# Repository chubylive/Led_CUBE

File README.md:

Led_CUBE
========

rgb led cube

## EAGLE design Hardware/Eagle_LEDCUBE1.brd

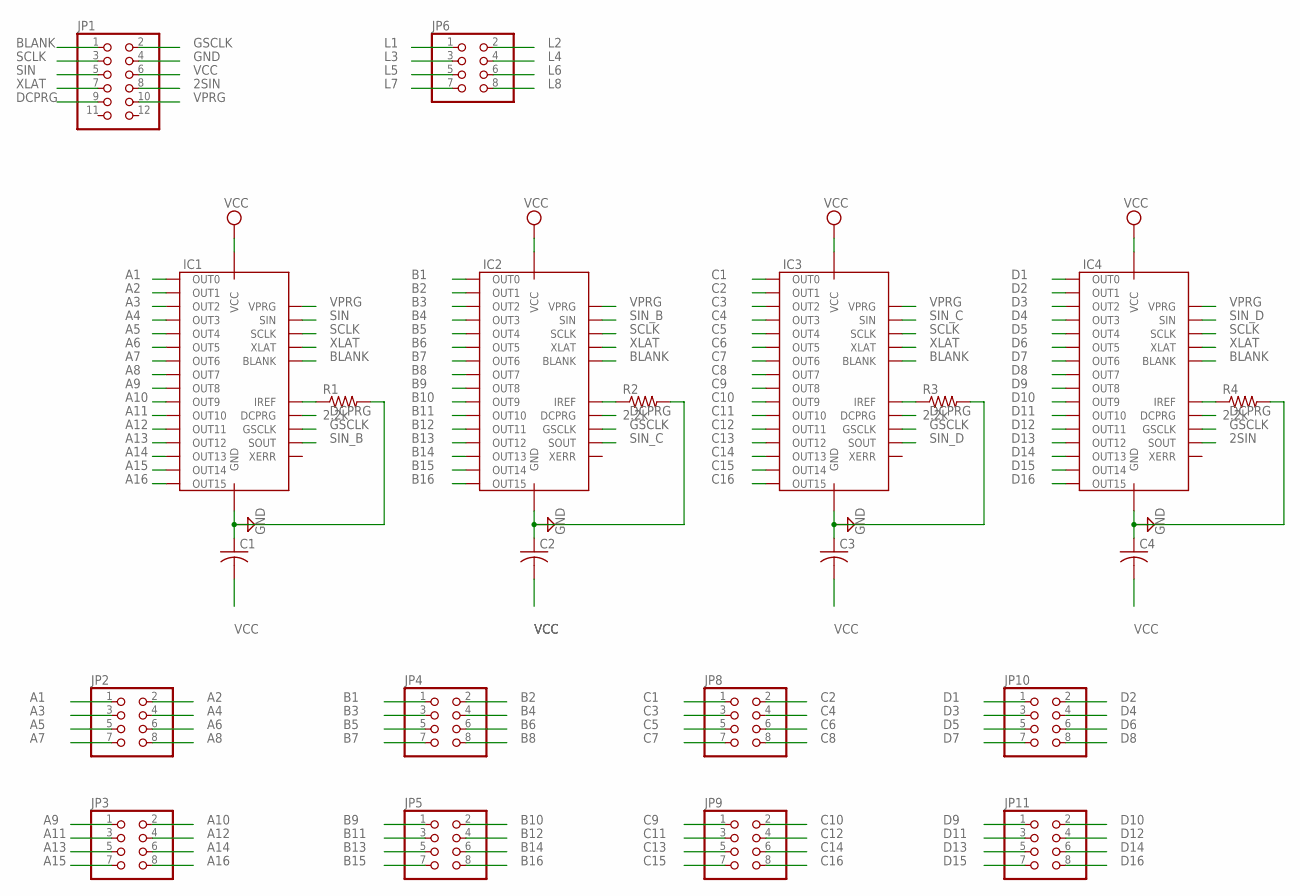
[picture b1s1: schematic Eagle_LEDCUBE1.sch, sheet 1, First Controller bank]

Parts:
C1, C2, C3, C4: C-USC0805K; C0805K
IC1, IC2, IC3, IC4: IC-PACKAGE_DIL28-1; IC-SSOP28
JP1: PINHD-2X6; 2X06
JP2, JP3, JP4, JP5, JP6, JP8, JP9, JP10, JP11: PINHD-2X4; 2X04
R1, R2, R3, R4: 2.2k; R0805

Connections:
2SIN: IC4.24 (SOUT), JP1.8; also elsewhere on the board
A1: IC1.7 (OUT0), JP2.1
A2: IC1.8 (OUT1), JP2.2
A3: IC1.9 (OUT2), JP2.3
A4: IC1.10 (OUT3), JP2.4
A5: IC1.11 (OUT4), JP2.5
A6: IC1.12 (OUT5), JP2.6
A7: IC1.13 (OUT6), JP2.7
A8: IC1.14 (OUT7), JP2.8
A9: IC1.15 (OUT8), JP3.1
A10: IC1.16 (OUT9), JP3.2
A11: IC1.17 (OUT10), JP3.3
A12: IC1.18 (OUT11), JP3.4
A13: IC1.19 (OUT12), JP3.5
A14: IC1.20 (OUT13), JP3.6
A15: IC1.21 (OUT14), JP3.7
A16: IC1.22 (OUT15), JP3.8
B1: IC2.7 (OUT0), JP4.1
B2: IC2.8 (OUT1), JP4.2
B3: IC2.9 (OUT2), JP4.3
B4: IC2.10 (OUT3), JP4.4
B5: IC2.11 (OUT4), JP4.5
B6: IC2.12 (OUT5), JP4.6
B7: IC2.13 (OUT6), JP4.7
B8: IC2.14 (OUT7), JP4.8
B9: IC2.15 (OUT8), JP5.1
B10: IC2.16 (OUT9), JP5.2
B11: IC2.17 (OUT10), JP5.3
B12: IC2.18 (OUT11), JP5.4
B13: IC2.19 (OUT12), JP5.5
B14: IC2.20 (OUT13), JP5.6
B15: IC2.21 (OUT14), JP5.7
B16: IC2.22 (OUT15), JP5.8
BLANK: IC1.2 (BLANK), IC2.2 (BLANK), IC3.2 (BLANK), IC4.2 (BLANK), JP1.1; also elsewhere on the board
C1: IC3.7 (OUT0), JP8.1
C2: IC3.8 (OUT1), JP8.2
C3: IC3.9 (OUT2), JP8.3
C4: IC3.10 (OUT3), JP8.4
C5: IC3.11 (OUT4), JP8.5
C6: IC3.12 (OUT5), JP8.6
C7: IC3.13 (OUT6), JP8.7
C8: IC3.14 (OUT7), JP8.8
C9: IC3.15 (OUT8), JP9.1
C10: IC3.16 (OUT9), JP9.2
C11: IC3.17 (OUT10), JP9.3
C12: IC3.18 (OUT11), JP9.4
C13: IC3.19 (OUT12), JP9.5
C14: IC3.20 (OUT13), JP9.6
C15: IC3.21 (OUT14), JP9.7
C16: IC3.22 (OUT15), JP9.8
D1: IC4.7 (OUT0), JP10.1
D2: IC4.8 (OUT1), JP10.2
D3: IC4.9 (OUT2), JP10.3
D4: IC4.10 (OUT3), JP10.4
D5: IC4.11 (OUT4), JP10.5
D6: IC4.12 (OUT5), JP10.6
D7: IC4.13 (OUT6), JP10.7
D8: IC4.14 (OUT7), JP10.8
D9: IC4.15 (OUT8), JP11.1
D10: IC4.16 (OUT9), JP11.2
D11: IC4.17 (OUT10), JP11.3
D12: IC4.18 (OUT11), JP11.4
D13: IC4.19 (OUT12), JP11.5
D14: IC4.20 (OUT13), JP11.6
D15: IC4.21 (OUT14), JP11.7
D16: IC4.22 (OUT15), JP11.8
DCPRG: IC1.26 (DCPRG), IC2.26 (DCPRG), IC3.26 (DCPRG), IC4.26 (DCPRG), JP1.9; also elsewhere on the board
GND: C1.1, C2.1, C3.1, C4.1, IC1.1 (GND), IC2.1 (GND), IC3.1 (GND), IC4.1 (GND), JP1.4, R1.2, R2.2, R3.2, R4.2; also elsewhere on the board
GSCLK: IC1.25 (GSCLK), IC2.25 (GSCLK), IC3.25 (GSCLK), IC4.25 (GSCLK), JP1.2; also elsewhere on the board
L1: JP6.1; also elsewhere on the board
L2: JP6.2; also elsewhere on the board
L3: JP6.3; also elsewhere on the board
L4: JP6.4; also elsewhere on the board
L5: JP6.5; also elsewhere on the board
L6: JP6.6; also elsewhere on the board
L7: JP6.7; also elsewhere on the board
L8: JP6.8; also elsewhere on the board
unnamed: IC1.27 (IREF), R1.1
unnamed: IC2.27 (IREF), R2.1
unnamed: IC3.27 (IREF), R3.1
unnamed: IC4.27 (IREF), R4.1
SCLK: IC1.4 (SCLK), IC2.4 (SCLK), IC3.4 (SCLK), IC4.4 (SCLK), JP1.3; also elsewhere on the board
SIN: IC1.5 (SIN), JP1.5; also elsewhere on the board
SIN_B: IC1.24 (SOUT), IC2.5 (SIN)
SIN_C: IC2.24 (SOUT), IC3.5 (SIN)
SIN_D: IC3.24 (SOUT), IC4.5 (SIN)
VCC: C1.2, C2.2, C3.2, C4.2, IC1.28 (VCC), IC2.28 (VCC), IC3.28 (VCC), IC4.28 (VCC), JP1.6; also elsewhere on the board
VPRG: IC1.6 (VPRG), IC2.6 (VPRG), IC3.6 (VPRG), IC4.6 (VPRG), JP1.10; also elsewhere on the board
XLAT: IC1.3 (XLAT), IC2.3 (XLAT), IC3.3 (XLAT), IC4.3 (XLAT), JP1.7; also elsewhere on the board

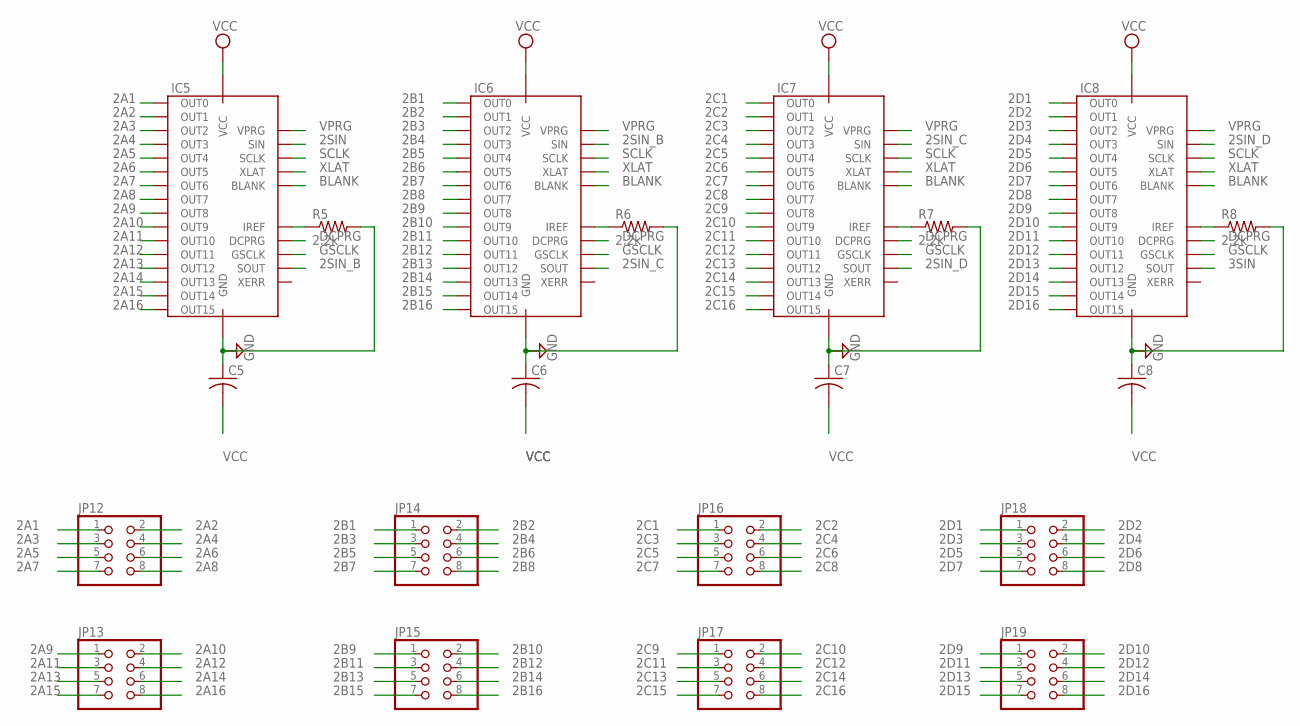
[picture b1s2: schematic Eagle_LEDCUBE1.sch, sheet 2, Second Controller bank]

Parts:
C5, C6, C7, C8: C-USC0805K; C0805K
IC5, IC6, IC7, IC8: IC-PACKAGE_DIL28-1; IC-SSOP28
JP12, JP13, JP14, JP15, JP16, JP17, JP18, JP19: PINHD-2X4; 2X04
R5, R6, R7, R8: 2.2k; R0805

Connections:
2A1: IC5.7 (OUT0), JP12.1
2A2: IC5.8 (OUT1), JP12.2
2A3: IC5.9 (OUT2), JP12.3
2A4: IC5.10 (OUT3), JP12.4
2A5: IC5.11 (OUT4), JP12.5
2A6: IC5.12 (OUT5), JP12.6
2A7: IC5.13 (OUT6), JP12.7
2A8: IC5.14 (OUT7), JP12.8
2A9: IC5.15 (OUT8), JP13.1
2A10: IC5.16 (OUT9), JP13.2
2A11: IC5.17 (OUT10), JP13.3
2A12: IC5.18 (OUT11), JP13.4
2A13: IC5.19 (OUT12), JP13.5
2A14: IC5.20 (OUT13), JP13.6
2A15: IC5.21 (OUT14), JP13.7
2A16: IC5.22 (OUT15), JP13.8
2B1: IC6.7 (OUT0), JP14.1
2B2: IC6.8 (OUT1), JP14.2
2B3: IC6.9 (OUT2), JP14.3
2B4: IC6.10 (OUT3), JP14.4
2B5: IC6.11 (OUT4), JP14.5
2B6: IC6.12 (OUT5), JP14.6
2B7: IC6.13 (OUT6), JP14.7
2B8: IC6.14 (OUT7), JP14.8
2B9: IC6.15 (OUT8), JP15.1
2B10: IC6.16 (OUT9), JP15.2
2B11: IC6.17 (OUT10), JP15.3
2B12: IC6.18 (OUT11), JP15.4
2B13: IC6.19 (OUT12), JP15.5
2B14: IC6.20 (OUT13), JP15.6
2B15: IC6.21 (OUT14), JP15.7
2B16: IC6.22 (OUT15), JP15.8
2C1: IC7.7 (OUT0), JP16.1
2C2: IC7.8 (OUT1), JP16.2
2C3: IC7.9 (OUT2), JP16.3
2C4: IC7.10 (OUT3), JP16.4
2C5: IC7.11 (OUT4), JP16.5
2C6: IC7.12 (OUT5), JP16.6
2C7: IC7.13 (OUT6), JP16.7
2C8: IC7.14 (OUT7), JP16.8
2C9: IC7.15 (OUT8), JP17.1
2C10: IC7.16 (OUT9), JP17.2
2C11: IC7.17 (OUT10), JP17.3
2C12: IC7.18 (OUT11), JP17.4
2C13: IC7.19 (OUT12), JP17.5
2C14: IC7.20 (OUT13), JP17.6
2C15: IC7.21 (OUT14), JP17.7
2C16: IC7.22 (OUT15), JP17.8
2D1: IC8.7 (OUT0), JP18.1
2D2: IC8.8 (OUT1), JP18.2
2D3: IC8.9 (OUT2), JP18.3
2D4: IC8.10 (OUT3), JP18.4
2D5: IC8.11 (OUT4), JP18.5
2D6: IC8.12 (OUT5), JP18.6
2D7: IC8.13 (OUT6), JP18.7
2D8: IC8.14 (OUT7), JP18.8
2D9: IC8.15 (OUT8), JP19.1
2D10: IC8.16 (OUT9), JP19.2
2D11: IC8.17 (OUT10), JP19.3
2D12: IC8.18 (OUT11), JP19.4
2D13: IC8.19 (OUT12), JP19.5
2D14: IC8.20 (OUT13), JP19.6
2D15: IC8.21 (OUT14), JP19.7
2D16: IC8.22 (OUT15), JP19.8
2SIN: IC5.5 (SIN); also elsewhere on the board
2SIN_B: IC5.24 (SOUT), IC6.5 (SIN)
2SIN_C: IC6.24 (SOUT), IC7.5 (SIN)
2SIN_D: IC7.24 (SOUT), IC8.5 (SIN)
3SIN: IC8.24 (SOUT); also elsewhere on the board
BLANK: IC5.2 (BLANK), IC6.2 (BLANK), IC7.2 (BLANK), IC8.2 (BLANK); also elsewhere on the board
DCPRG: IC5.26 (DCPRG), IC6.26 (DCPRG), IC7.26 (DCPRG), IC8.26 (DCPRG); also elsewhere on the board
GND: C5.1, C6.1, C7.1, C8.1, IC5.1 (GND), IC6.1 (GND), IC7.1 (GND), IC8.1 (GND), R5.2, R6.2, R7.2, R8.2; also elsewhere on the board
GSCLK: IC5.25 (GSCLK), IC6.25 (GSCLK), IC7.25 (GSCLK), IC8.25 (GSCLK); also elsewhere on the board
unnamed: IC5.27 (IREF), R5.1
unnamed: IC6.27 (IREF), R6.1
unnamed: IC7.27 (IREF), R7.1
unnamed: IC8.27 (IREF), R8.1
SCLK: IC5.4 (SCLK), IC6.4 (SCLK), IC7.4 (SCLK), IC8.4 (SCLK); also elsewhere on the board
VCC: C5.2, C6.2, C7.2, C8.2, IC5.28 (VCC), IC6.28 (VCC), IC7.28 (VCC), IC8.28 (VCC); also elsewhere on the board
VPRG: IC5.6 (VPRG), IC6.6 (VPRG), IC7.6 (VPRG), IC8.6 (VPRG); also elsewhere on the board
XLAT: IC5.3 (XLAT), IC6.3 (XLAT), IC7.3 (XLAT), IC8.3 (XLAT); also elsewhere on the board

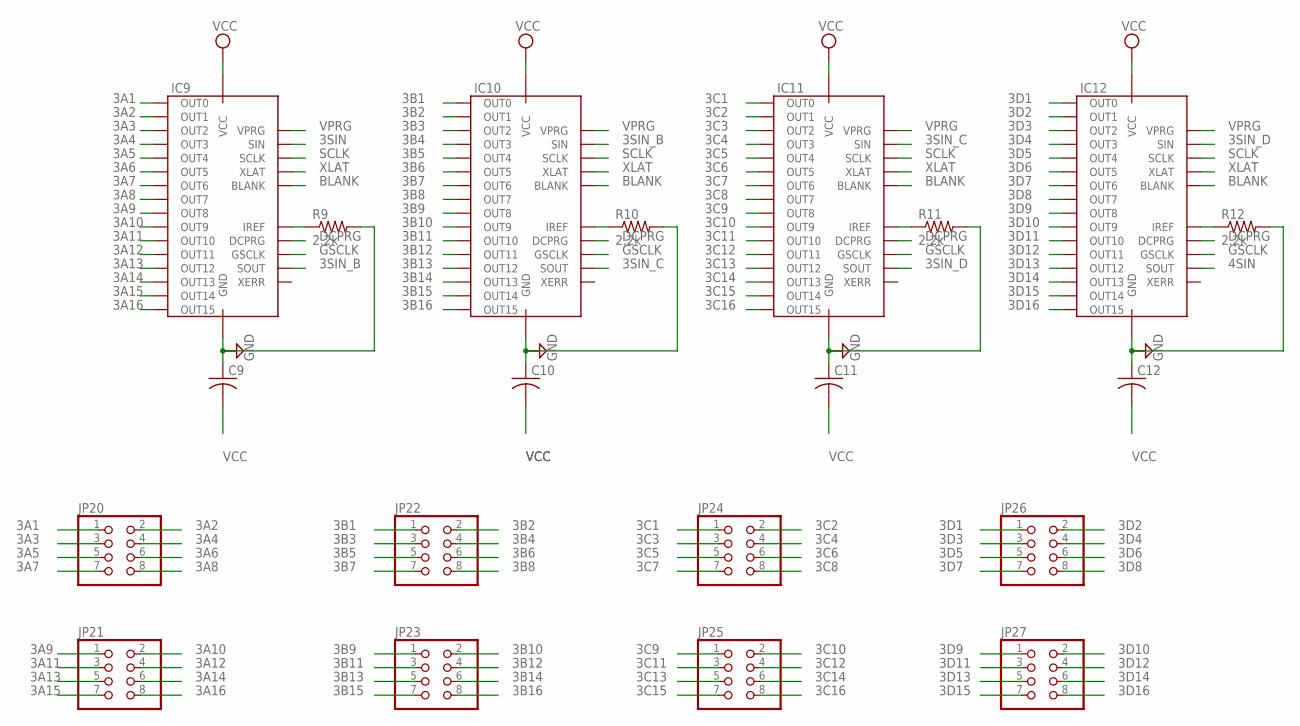
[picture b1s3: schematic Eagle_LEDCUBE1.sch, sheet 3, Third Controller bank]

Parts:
C9, C10, C11, C12: C-USC0805K; C0805K
IC9, IC10, IC11, IC12: IC-PACKAGE_DIL28-1; IC-SSOP28
JP20, JP21, JP22, JP23, JP24, JP25, JP26, JP27: PINHD-2X4; 2X04
R9, R10, R11, R12: 2.2k; R0805

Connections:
3A1: IC9.7 (OUT0), JP20.1
3A2: IC9.8 (OUT1), JP20.2
3A3: IC9.9 (OUT2), JP20.3
3A4: IC9.10 (OUT3), JP20.4
3A5: IC9.11 (OUT4), JP20.5
3A6: IC9.12 (OUT5), JP20.6
3A7: IC9.13 (OUT6), JP20.7
3A8: IC9.14 (OUT7), JP20.8
3A9: IC9.15 (OUT8), JP21.1
3A10: IC9.16 (OUT9), JP21.2
3A11: IC9.17 (OUT10), JP21.3
3A12: IC9.18 (OUT11), JP21.4
3A13: IC9.19 (OUT12), JP21.5
3A14: IC9.20 (OUT13), JP21.6
3A15: IC9.21 (OUT14), JP21.7
3A16: IC9.22 (OUT15), JP21.8
3B1: IC10.7 (OUT0), JP22.1
3B2: IC10.8 (OUT1), JP22.2
3B3: IC10.9 (OUT2), JP22.3
3B4: IC10.10 (OUT3), JP22.4
3B5: IC10.11 (OUT4), JP22.5
3B6: IC10.12 (OUT5), JP22.6
3B7: IC10.13 (OUT6), JP22.7
3B8: IC10.14 (OUT7), JP22.8
3B9: IC10.15 (OUT8), JP23.1
3B10: IC10.16 (OUT9), JP23.2
3B11: IC10.17 (OUT10), JP23.3
3B12: IC10.18 (OUT11), JP23.4
3B13: IC10.19 (OUT12), JP23.5
3B14: IC10.20 (OUT13), JP23.6
3B15: IC10.21 (OUT14), JP23.7
3B16: IC10.22 (OUT15), JP23.8
3C1: IC11.7 (OUT0), JP24.1
3C2: IC11.8 (OUT1), JP24.2
3C3: IC11.9 (OUT2), JP24.3
3C4: IC11.10 (OUT3), JP24.4
3C5: IC11.11 (OUT4), JP24.5
3C6: IC11.12 (OUT5), JP24.6
3C7: IC11.13 (OUT6), JP24.7
3C8: IC11.14 (OUT7), JP24.8
3C9: IC11.15 (OUT8), JP25.1
3C10: IC11.16 (OUT9), JP25.2
3C11: IC11.17 (OUT10), JP25.3
3C12: IC11.18 (OUT11), JP25.4
3C13: IC11.19 (OUT12), JP25.5
3C14: IC11.20 (OUT13), JP25.6
3C15: IC11.21 (OUT14), JP25.7
3C16: IC11.22 (OUT15), JP25.8
3D1: IC12.7 (OUT0), JP26.1
3D2: IC12.8 (OUT1), JP26.2
3D3: IC12.9 (OUT2), JP26.3
3D4: IC12.10 (OUT3), JP26.4
3D5: IC12.11 (OUT4), JP26.5
3D6: IC12.12 (OUT5), JP26.6
3D7: IC12.13 (OUT6), JP26.7
3D8: IC12.14 (OUT7), JP26.8
3D9: IC12.15 (OUT8), JP27.1
3D10: IC12.16 (OUT9), JP27.2
3D11: IC12.17 (OUT10), JP27.3
3D12: IC12.18 (OUT11), JP27.4
3D13: IC12.19 (OUT12), JP27.5
3D14: IC12.20 (OUT13), JP27.6
3D15: IC12.21 (OUT14), JP27.7
3D16: IC12.22 (OUT15), JP27.8
3SIN: IC9.5 (SIN); also elsewhere on the board
3SIN_B: IC9.24 (SOUT), IC10.5 (SIN)
3SIN_C: IC10.24 (SOUT), IC11.5 (SIN)
3SIN_D: IC11.24 (SOUT), IC12.5 (SIN)
4SIN: IC12.24 (SOUT)
BLANK: IC9.2 (BLANK), IC10.2 (BLANK), IC11.2 (BLANK), IC12.2 (BLANK); also elsewhere on the board
DCPRG: IC9.26 (DCPRG), IC10.26 (DCPRG), IC11.26 (DCPRG), IC12.26 (DCPRG); also elsewhere on the board
GND: C9.1, C10.1, C11.1, C12.1, IC9.1 (GND), IC10.1 (GND), IC11.1 (GND), IC12.1 (GND), R9.2, R10.2, R11.2, R12.2; also elsewhere on the board
GSCLK: IC9.25 (GSCLK), IC10.25 (GSCLK), IC11.25 (GSCLK), IC12.25 (GSCLK); also elsewhere on the board
unnamed: IC9.27 (IREF), R9.1
unnamed: IC10.27 (IREF), R10.1
unnamed: IC11.27 (IREF), R11.1
unnamed: IC12.27 (IREF), R12.1
SCLK: IC9.4 (SCLK), IC10.4 (SCLK), IC11.4 (SCLK), IC12.4 (SCLK); also elsewhere on the board
VCC: C9.2, C10.2, C11.2, C12.2, IC9.28 (VCC), IC10.28 (VCC), IC11.28 (VCC), IC12.28 (VCC); also elsewhere on the board
VPRG: IC9.6 (VPRG), IC10.6 (VPRG), IC11.6 (VPRG), IC12.6 (VPRG); also elsewhere on the board
XLAT: IC9.3 (XLAT), IC10.3 (XLAT), IC11.3 (XLAT), IC12.3 (XLAT); also elsewhere on the board

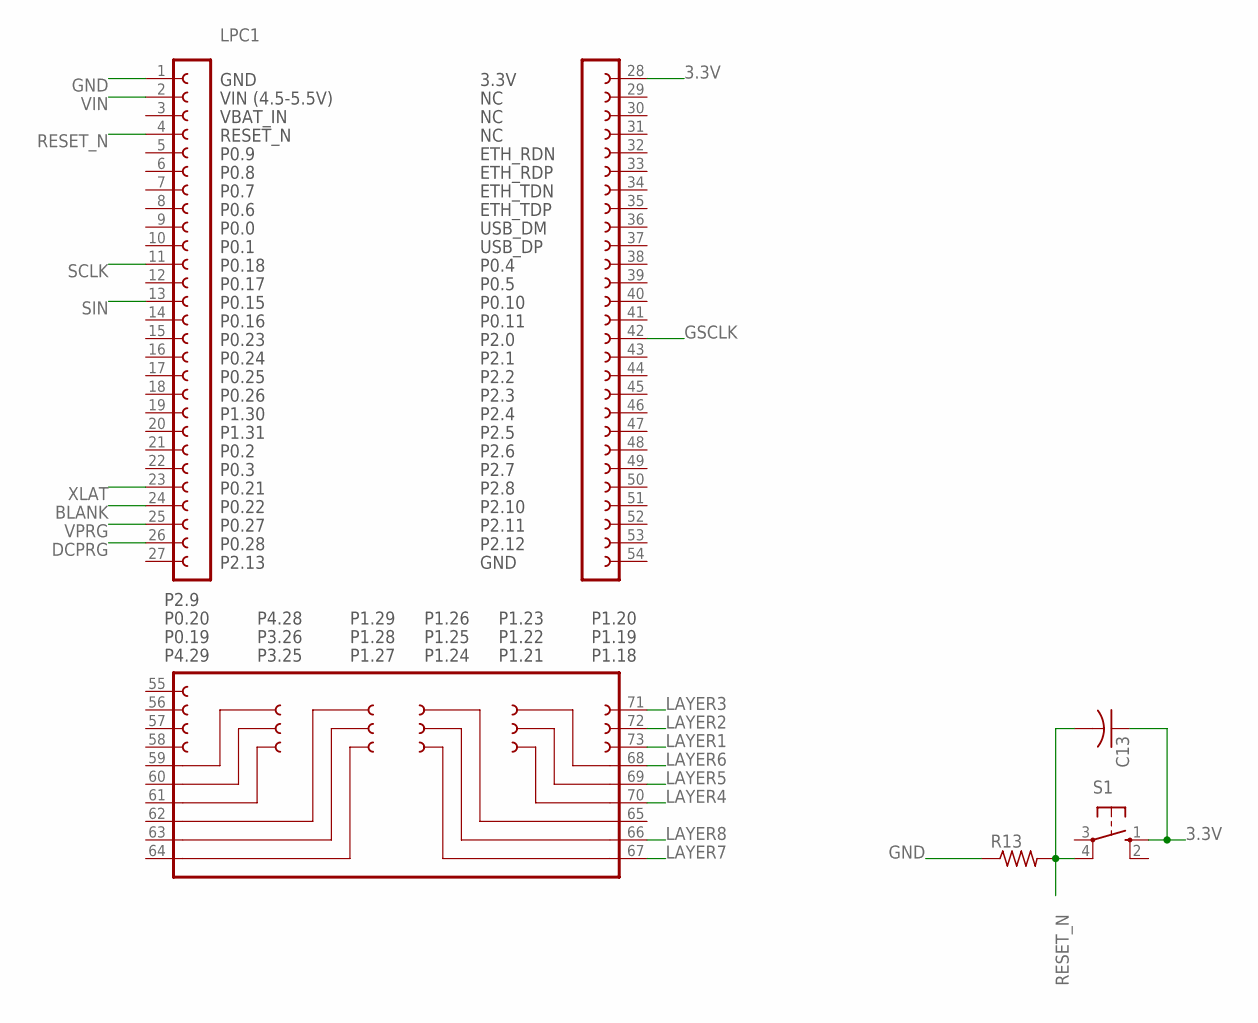
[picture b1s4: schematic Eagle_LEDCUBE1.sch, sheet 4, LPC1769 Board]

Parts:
C13: C-USC0805K; C0805K
LPC1: LPCXPRESSO_LPC1769
R13: R-US_R0805; R0805
S1: 10-XX; B3F-10XX

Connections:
3.3V: C13.1, LPC1.28, S1.1 (S)
BLANK: LPC1.24; also elsewhere on the board
DCPRG: LPC1.26; also elsewhere on the board
GND: LPC1.1, R13.1; also elsewhere on the board
GSCLK: LPC1.42; also elsewhere on the board
LAYER1: LPC1.73; also elsewhere on the board
LAYER2: LPC1.72; also elsewhere on the board
LAYER3: LPC1.71; also elsewhere on the board
LAYER4: LPC1.70; also elsewhere on the board
LAYER5: LPC1.69; also elsewhere on the board
LAYER6: LPC1.68; also elsewhere on the board
LAYER7: LPC1.67; also elsewhere on the board
LAYER8: LPC1.66; also elsewhere on the board
RESET_N: C13.2, LPC1.4, R13.2, S1.4 (P1)
SCLK: LPC1.11; also elsewhere on the board
SIN: LPC1.13; also elsewhere on the board
VIN: LPC1.2
VPRG: LPC1.25; also elsewhere on the board
XLAT: LPC1.23; also elsewhere on the board

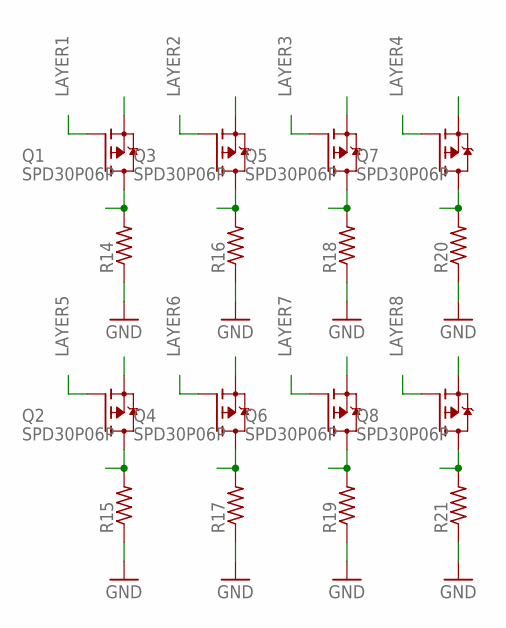
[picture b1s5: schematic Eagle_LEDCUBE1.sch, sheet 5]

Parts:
Q1, Q2, Q3, Q4, Q5, Q6, Q7, Q8: SPD30P06P; TO251AA
R14, R15, R16, R17, R18, R19, R20, R21: R-US_R0805; R0805

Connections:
GND: R14.1, R15.1, R16.1, R17.1, R18.1, R19.1, R20.1, R21.1; also elsewhere on the board
L1: Q1.2 (D), R14.2; also elsewhere on the board
L2: Q3.2 (D), R16.2; also elsewhere on the board
L3: Q5.2 (D), R18.2; also elsewhere on the board
L4: Q7.2 (D), R20.2; also elsewhere on the board
L5: Q2.2 (D), R15.2; also elsewhere on the board
L6: Q4.2 (D), R17.2; also elsewhere on the board
L7: Q6.2 (D), R19.2; also elsewhere on the board
L8: Q8.2 (D), R21.2; also elsewhere on the board
LAYER1: Q1.1 (G); also elsewhere on the board
LAYER2: Q3.1 (G); also elsewhere on the board
LAYER3: Q5.1 (G); also elsewhere on the board
LAYER4: Q7.1 (G); also elsewhere on the board
LAYER5: Q2.1 (G); also elsewhere on the board
LAYER6: Q4.1 (G); also elsewhere on the board
LAYER7: Q6.1 (G); also elsewhere on the board
LAYER8: Q8.1 (G); also elsewhere on the board

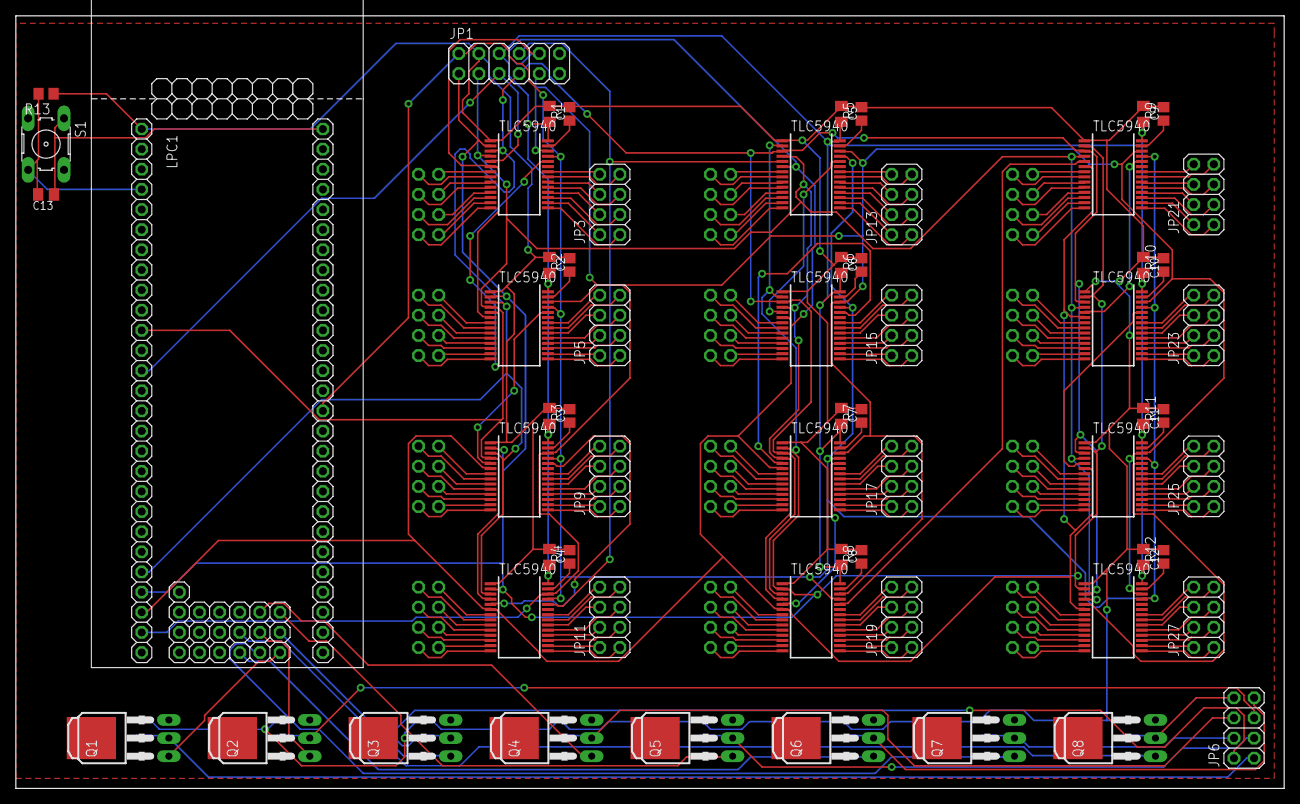
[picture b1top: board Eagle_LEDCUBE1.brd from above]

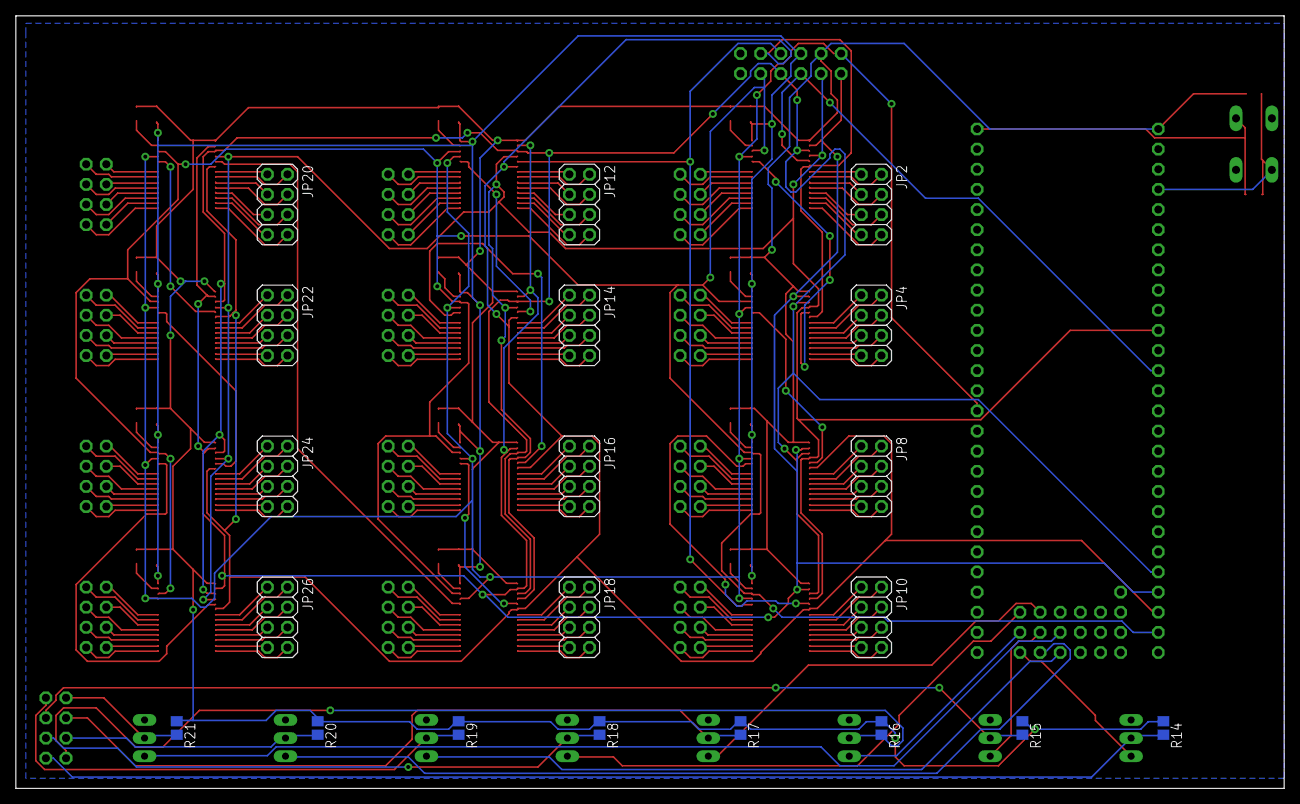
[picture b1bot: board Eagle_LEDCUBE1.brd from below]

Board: 2 copper layers, 160.0 x 97.5 mm, 82 parts (20 on the bottom side), 242 nets.

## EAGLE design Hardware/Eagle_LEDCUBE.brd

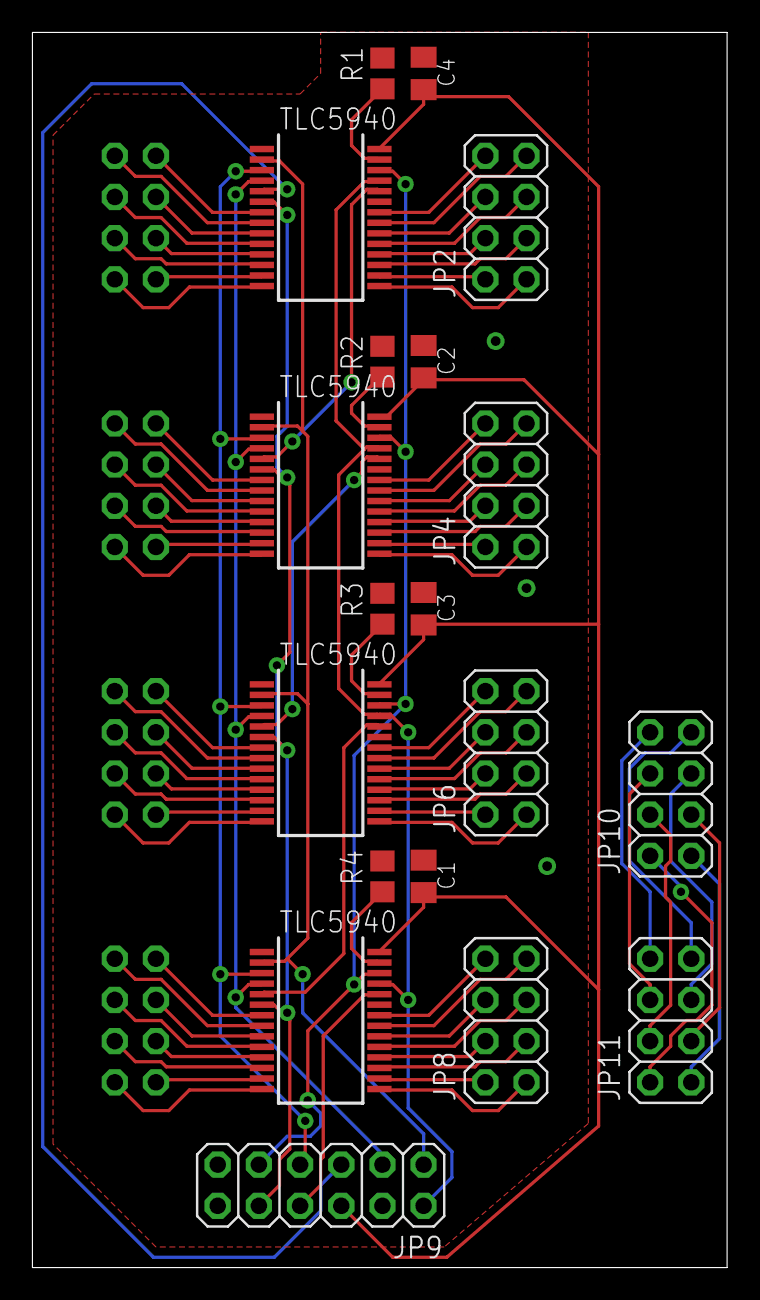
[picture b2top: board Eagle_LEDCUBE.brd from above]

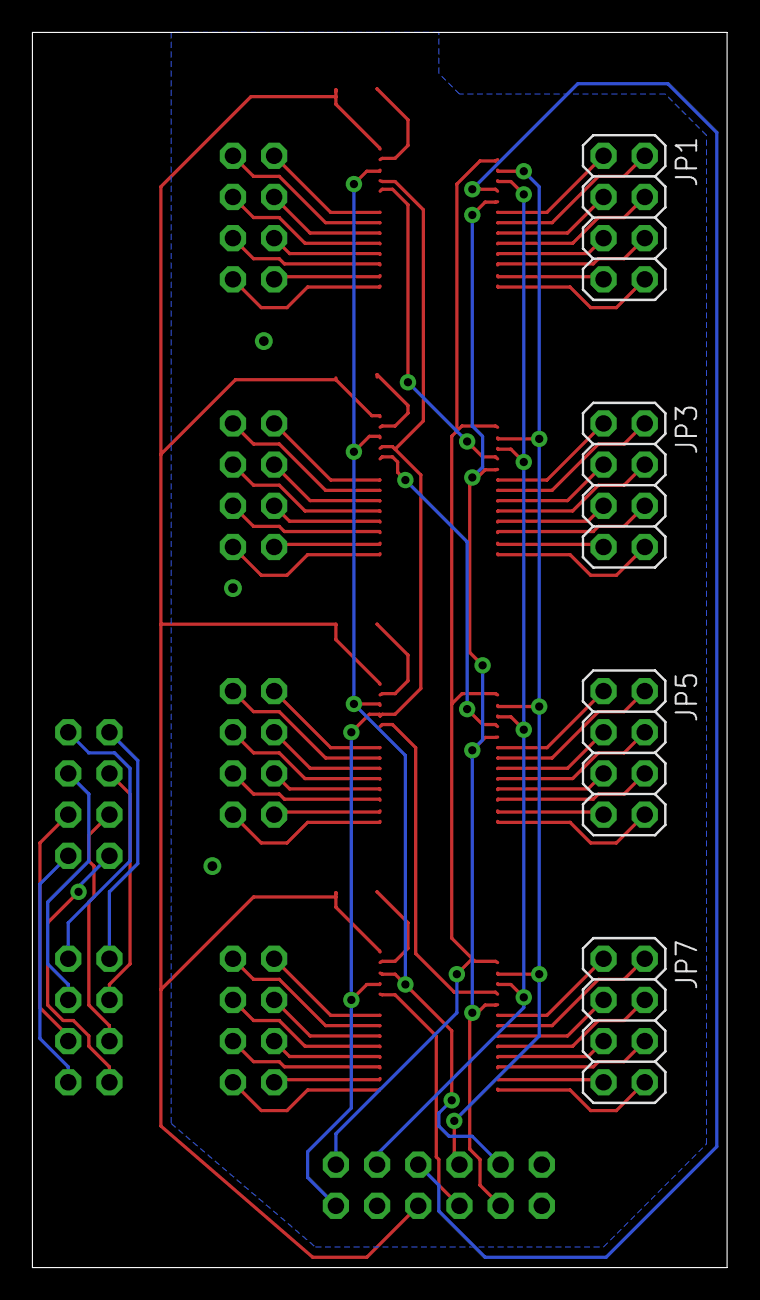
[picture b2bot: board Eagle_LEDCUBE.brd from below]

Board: 2 copper layers, 42.8 x 76.2 mm, 23 parts (4 on the bottom side), 89 nets.

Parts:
C1, C2, C3, C4: C0805K
IC1, IC2, IC3, IC4: IC-SSOP28
JP1, JP2, JP3, JP4, JP5, JP6, JP7, JP8, JP10, JP11: 2X04
JP9: 2X06
R1, R2, R3, R4: 2.2k; R0805

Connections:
A1: IC1.7, JP1.1
A2: IC1.8, JP1.2
A3: IC1.9, JP1.3
A4: IC1.10, JP1.4
A5: IC1.11, JP1.5
A6: IC1.12, JP1.6
A7: IC1.13, JP1.7
A8: IC1.14, JP1.8
A9: IC1.15, JP2.1
A10: IC1.16, JP2.2
A11: IC1.17, JP2.3
A12: IC1.18, JP2.4
A13: IC1.19, JP2.5
A14: IC1.20, JP2.6
A15: IC1.21, JP2.7
A16: IC1.22, JP2.8
B1: IC2.7, JP3.1
B2: IC2.8, JP3.2
B3: IC2.9, JP3.3
B4: IC2.10, JP3.4
B5: IC2.11, JP3.5
B6: IC2.12, JP3.6
B7: IC2.13, JP3.7
B8: IC2.14, JP3.8
B9: IC2.15, JP4.1
B10: IC2.16, JP4.2
B11: IC2.17, JP4.3
B12: IC2.18, JP4.4
B13: IC2.19, JP4.5
B14: IC2.20, JP4.6
B15: IC2.21, JP4.7
B16: IC2.22, JP4.8
BLANK: IC1.2, IC2.2, IC3.2, IC4.2, JP9.1
C1: IC3.7, JP5.1
C2: IC3.8, JP5.2
C3: IC3.9, JP5.3
C4: IC3.10, JP5.4
C5: IC3.11, JP5.5
C6: IC3.12, JP5.6
C7: IC3.13, JP5.7
C8: IC3.14, JP5.8
C9: IC3.15, JP6.1
C10: IC3.16, JP6.2
C11: IC3.17, JP6.3
C12: IC3.18, JP6.4
C13: IC3.19, JP6.5
C14: IC3.20, JP6.6
C15: IC3.21, JP6.7
C16: IC3.22, JP6.8
D1: IC4.7, JP7.1
D2: IC4.8, JP7.2
D3: IC4.9, JP7.3
D4: IC4.10, JP7.4
D5: IC4.11, JP7.5
D6: IC4.12, JP7.6
D7: IC4.13, JP7.7
D8: IC4.14, JP7.8
D9: IC4.15, JP8.1
D10: IC4.16, JP8.2
D11: IC4.17, JP8.3
D12: IC4.18, JP8.4
D13: IC4.19, JP8.5
D14: IC4.20, JP8.6
D15: IC4.21, JP8.7
D16: IC4.22, JP8.8
DCPRG: IC1.26, IC2.26, IC3.26, IC4.26, JP9.9
GND: C1.1, C2.1, C3.1, C4.1, IC1.1, IC2.1, IC3.1, IC4.1, JP9.4, R1.2, R2.2, R3.2, R4.2
GSCLK: IC1.25, IC2.25, IC3.25, IC4.25, JP9.2
L1: JP10.1, JP11.1
L2: JP10.2, JP11.2
L3: JP10.3, JP11.3
L4: JP10.4, JP11.4
L5: JP10.5, JP11.5
L6: JP10.6, JP11.6
L7: JP10.7, JP11.7
L8: JP10.8, JP11.8
unnamed: IC1.27, R1.1
unnamed: IC2.27, R2.1
unnamed: IC3.27, R3.1
unnamed: IC4.27, R4.1
SCLK: IC1.4, IC2.4, IC3.4, IC4.4, JP9.3
SIN: IC1.5, JP9.5
SIN_B: IC1.24, IC2.5
SIN_C: IC2.24, IC3.5
SIN_D: IC3.24, IC4.5
SIN_E: IC4.24, JP9.8
VCC: C1.2, C2.2, C3.2, C4.2, IC1.28, IC2.28, IC3.28, IC4.28, JP9.6
VPRG: IC1.6, IC2.6, IC3.6, IC4.6, JP9.10
XLAT: IC1.3, IC2.3, IC3.3, IC4.3, JP9.7

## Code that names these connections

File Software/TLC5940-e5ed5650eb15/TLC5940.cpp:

#include "TLC5940.h"

TLC5940::TLC5940(PinName SCLK, PinName MOSI, PinName GSCLK, PinName BLANK, 
                 PinName XLAT, PinName DCPRG, PinName VPRG, const int number) : number(number),
                                                                                spi(MOSI, NC, SCLK),
                                                                                gsclk(GSCLK),
                                                                                blank(BLANK),
                                                                                xlat(XLAT),
                                                                                dcprg(DCPRG),
                                                                                vprg(VPRG),
                                                                                newGSData(false),
                                                                                newDCData(false),
                                                                                need_xlat(false)
{   
    // Configure SPI to 12 bits and SPI_SPEED
    spi.format(12, 0);
    spi.frequency(SPI_SPEED);
    
    // Set output pin states
    dcprg = 0;
    vprg = 0;
    xlat = 0;
    blank = 1;
    
    // Call the reset function every 4096 PWM outputs
    reset_ticker.attach_us(this, &TLC5940::reset, (1000000.0/GSCLK_SPEED) * 4096.0);
    
    // Configure FastPWM output for GSCLK frequency at 50% duty cycle
    gsclk.period_us(1000000.0/(GSCLK_SPEED * 1.05));
    gsclk.write(.5);
}

void TLC5940::setNewGSData(unsigned short* data)
{
    gsBuffer = data;
    
    // Tell reset function that new GS data has been given
    newGSData = true;
}

void TLC5940::setNewDCData(unsigned char* data)
{
    dcBuffer = data;
    
    // Tell reset function that new DC data has been given
    newDCData = true;
}

void TLC5940::reset()
{
    gsclk.write(0);
    // Turn off LEDs
    blank = 1;
    
    // Virtual function that allows the next data chunk to be set after every GSCLK cycle
    // Useful for setting the next frame when multiplexing (e.g. LED matrices)
    setNextData();
    
    // Latch in data from previous cycle if needed
    if (need_xlat)
    {
        // Latch
        xlat = 1;
        xlat = 0;
        
        // Don't need to latch again
        need_xlat = false;
    }
    
    // Reset the screen so that it is updating while data is being sent
    blank = 0;
    gsclk.write(.5);
    
    // Do we have new DC data to send?
    if (newDCData)
    {
        // Set TLC5940 to accpet DC data
        vprg = 1;
        
        // Get DC data from registers instead of EEPROM (since we are sending data to the registers now)
        dcprg = 1;
        
        // Send DC data backwards - this makes the DC_buffer[0] index correspond to OUT0
        for (int i = (16 * number) - 1; i >= 0; i--)
        {
            // Assemble a 12 bit packet from two 6 bit chunks
            spi.write(((dcBuffer[i] & 0x3F) << 6) | (dcBuffer[i-1] & 0x3F));
            i--;
        }
        
        // Latch
        xlat = 1;
        xlat = 0;
        
        // No new data to send (we just sent it!)
        newDCData = false;
    }
    
    // Do we have new GS data to send?
    if (newGSData)
    {
        // Set TLC5940 to accept GS data
        vprg = 0;
        
        // Send GS data backwards - this makes the GS_buffer[0] index correspond to OUT0 
        for (int i = (16 * number) - 1; i >= 0; i--)
        {
            // Get the lower 12 bits of the buffer and send
            spi.write(gsBuffer[i] & 0xFFF);
        }
        
        // Latch after current GS data is done being displayed
        need_xlat = true;
        
        // No new data to send (we just sent it!)
        newGSData = false;
    }
}

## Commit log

2014-06-20 first commit:
2014-06-21 starting
2014-06-24 half board
2014-08-04 please be cool
2014-08-06 progress
2014-08-07 good day
2014-08-28 driver done
2014-09-03 progress on board
2015-01-03 add corrected TLC54940 code what remains is to scale things up
2015-01-06 moving from kicad to eagle. The boards came ba ck with crazy shorts in them so i am re-designing them in kicad.
2015-01-07 just updated code on laptop
2015-02-01 a whole of stuff. got layers working. need to fix mux data buffer. figure out possible refresh rates
2015-02-08 implementing shift 16
2015-02-08 added new files not tested:
2015-02-18 testing of 16bit buffer complete. Creating new branch from which all dev would continue from and next would be mutiplexing buffer test. Then animation harness dev.
2015-02-18 16 bit shiftout
2015-02-18 8 bit base mux
2015-02-18 16 bit TLC5940_SetAllGS does not work
2015-02-27 strange things happening
2015-02-27 ghosting between two layers
2015-02-27 possible bug ing SetColour3D_16. It does not seem to set 2,*,*
2015-02-27 seem 8bit is indeed to slow
2015-02-28 break; was casuing ghosting
2015-03-01 animation started
2015-03-14 animation with single board success
2015-03-15 new colourwheel
2015-03-28 sinwave buggy
2015-04-08 current board files
2015-04-08 seems to be already updated V1 board files
2015-04-17 animation harness structs
2015-04-25 last changes before 4-24-2015 pull
2015-04-25 harness 1.0
2015-05-01 xor buffer for animation overlay
2015-05-02 xor buff working
2015-05-21 animation framework 1.0
2015-05-27 main board v2
2015-05-29 coming along
2015-08-17 adding eagle board 10mm*20mm
2016-01-27 new board complete
2016-05-09 added object hash not tested
2018-04-09 start in project please try to create a running log so retrancy is easy
2018-09-04 2018 changes
2018-09-05 sphere bounce
